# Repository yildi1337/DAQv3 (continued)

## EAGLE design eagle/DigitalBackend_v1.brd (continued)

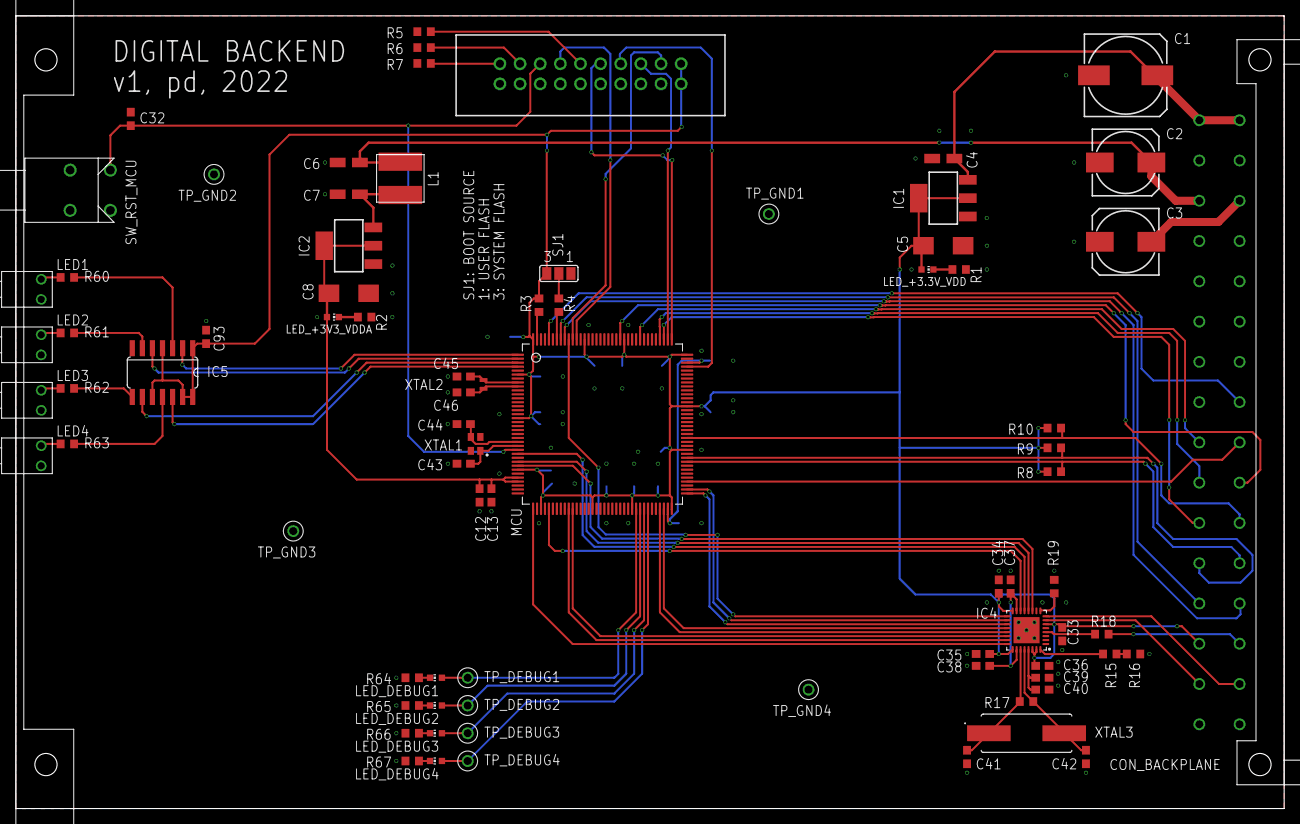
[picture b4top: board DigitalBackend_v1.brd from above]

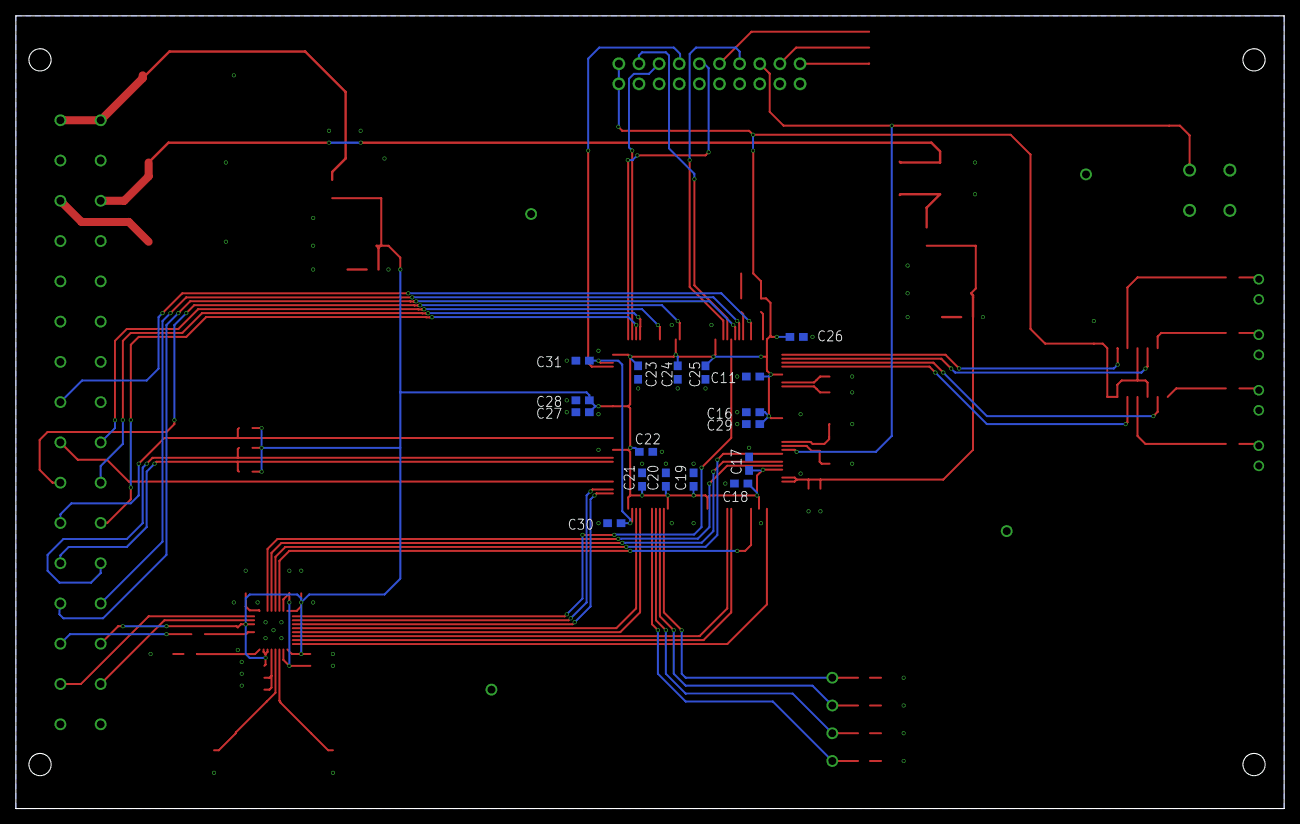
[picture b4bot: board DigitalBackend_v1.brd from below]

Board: 2 copper layers, 160.0 x 100.0 mm, 98 parts (17 on the bottom side), 80 nets.

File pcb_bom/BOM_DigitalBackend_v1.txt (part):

Stückliste exportiert aus D:/OneDrive/Elektronikprojekte/DAQ v3 STM32H7/Eagle/Digital Backend v1/DigitalBackend_v1.sch am 20.03.2022 16:16

Qty Value                           Device                          Package                         Parts                                                                                                   Description                          POPULARITY SPICEPREFIX
6                                   LEDCHIP-LED0603                 CHIP-LED0603                    LED_+3.3V_VDD, LED_+3V3_VDDA, LED_DEBUG1, LED_DEBUG2, LED_DEBUG3, LED_DEBUG4                            LED                                  26                    
4                                   RSPRO-1MM-TERMINAL-POST-2622034 RSPRO-1MM-TERMINAL-POST-2622034 TP_GND1, TP_GND2, TP_GND3, TP_GND4                                                                                                                                 
1                                   SJ2W                            SJ_2                            SJ1                                                                                                     SMD solder JUMPER                    7                     
1   09031326921                     09031326921                     09031326921                     CON_BACKPLANE                                                                                                                                                      
3   1.5k                            R-EU_R0603                      R0603                           R8, R9, R10                                                                                             RESISTOR, European symbol            70         R          
1   1.8k                            R-EU_R0603                      R0603                           R2                                                                                                      RESISTOR, European symbol            70         R          
1   1000u/16V                       CPOL-EU153CLV-1010              153CLV-1010                     C1                                                                                                      POLARIZED CAPACITOR, European symbol 0          C          
21  100n                            C-EUC0603                       C0603                           C13, C16, C17, C18, C19, C20, C21, C22, C23, C24, C25, C26, C28, C32, C33, C34, C35, C36, C37, C40, C93 CAPACITOR, European symbol           73         C          
1   100u                            VLS6045AF-101M                  VLS6045AF-101M                  L1                                                                                                                                                                 
2   100u/25V                        CPOL-EU153CLV-0810              153CLV-0810                     C2, C3                                                                                                  POLARIZED CAPACITOR, European symbol 4          C          
6   10k                             R-EU_R0603                      R0603                           R3, R4, R5, R6, R7, R16                                                                                 RESISTOR, European symbol            70         R          
3   10u                             CPOL-EUCT3216                   CT3216                          C4, C6, C7                                                                                              POLARIZED CAPACITOR, European symbol 1          C          
4   113-314-04                      113-314-04                      113-314-04                      LED1, LED2, LED3, LED4                                                                                                                                             
2   15p                             C-EUC0603                       C0603                           C45, C46                                                                                                CAPACITOR, European symbol           73         C          
1   1M                              R-EU_R0603                      R0603                           R17                                                                                                     RESISTOR, European symbol            70         R          
3   1u                              C-EUC0603                       C0603                           C11, C12, C27                                                                                           CAPACITOR, European symbol           73         C          
2   2.2u                            C-EUC0603                       C0603                           C30, C31                                                                                                CAPACITOR, European symbol           73         C          
2   22u                             CPOL-EUCT6032                   CT6032                          C5, C8                                                                                                  POLARIZED CAPACITOR, European symbol 2          C          
2   27p                             C-EUC0603                       C0603                           C41, C42                                                                                                CAPACITOR, European symbol           73         C          
1   2k                              R-EU_R0603                      R0603                           R15                                                                                                     RESISTOR, European symbol            70         R          
1   4.7k                            R-EU_R0603                      R0603                           R19                                                                                                     RESISTOR, European symbol            70         R          
3   4.7u                            C-EUC0603                       C0603                           C29, C38, C39                                                                                           CAPACITOR, European symbol           73         C          
2   5.6p                            C-EUC0603                       C0603                           C43, C44                                                                                                CAPACITOR, European symbol           73         C          
1   60807-011                       60807-011                       60807-011                       PCB_BRACKET                                                                                                                                                        
4   68                              R-EU_R0603                      R0603                           R60, R61, R62, R63                                                                                      RESISTOR, European symbol            70         R          
1   74LVC126AD,112                  74AC126D                        SO14                            IC5                                                                                                     Quad bus BUFFER, 3-state             0                     
5   750                             R-EU_R0603                      R0603                           R1, R64, R65, R66, R67                                                                                  RESISTOR, European symbol            70         R          
1   820                             R-EU_R0603                      R0603                           R18                                                                                                     RESISTOR, European symbol            70         R          
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
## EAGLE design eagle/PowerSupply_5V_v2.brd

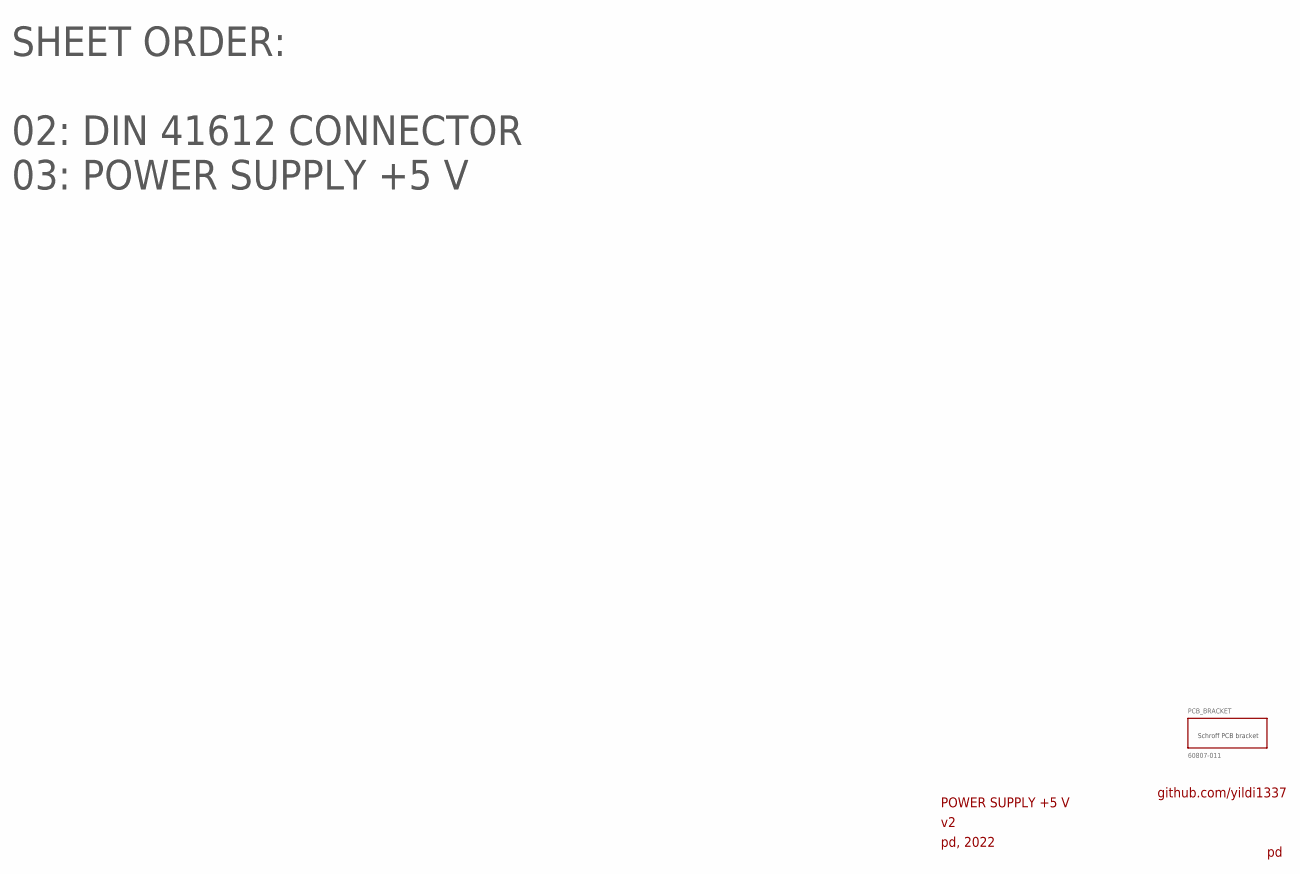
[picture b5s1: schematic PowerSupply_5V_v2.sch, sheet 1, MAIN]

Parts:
PCB_BRACKET: 60807-011

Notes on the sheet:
POWER SUPPLY +5 V
pd, 2022
github.com/yildi1337
SHEET ORDER: 02: DIN 41612 CONNECTOR 03: POWER SUPPLY +5 V

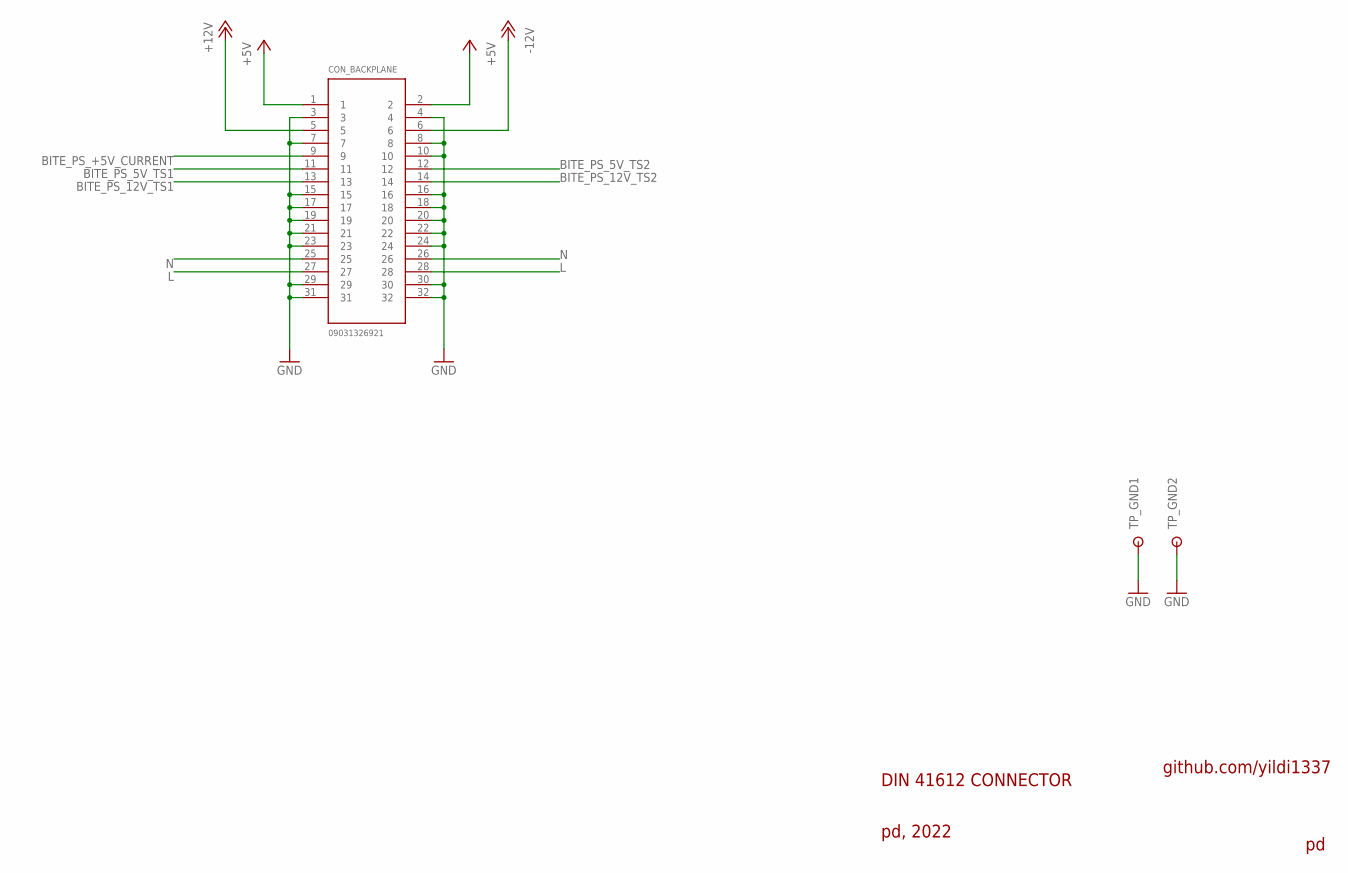
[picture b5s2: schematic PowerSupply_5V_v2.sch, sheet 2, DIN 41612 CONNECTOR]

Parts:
CON_BACKPLANE: 09031326921
TP_GND1, TP_GND2: RSPRO-1MM-TERMINAL-POST-2622034

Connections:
+5V: CON_BACKPLANE.1, CON_BACKPLANE.2; also elsewhere on the board
+12V: CON_BACKPLANE.5
-12V: CON_BACKPLANE.6
BITE_PS_5V_TS1: CON_BACKPLANE.11
BITE_PS_5V_TS2: CON_BACKPLANE.12
BITE_PS_12V_TS1: CON_BACKPLANE.13
BITE_PS_12V_TS2: CON_BACKPLANE.14
BITE_PS_+5V_CURRENT: CON_BACKPLANE.9
GND: CON_BACKPLANE.3, CON_BACKPLANE.4, CON_BACKPLANE.7, CON_BACKPLANE.8, CON_BACKPLANE.10, CON_BACKPLANE.15, CON_BACKPLANE.16, CON_BACKPLANE.17, CON_BACKPLANE.18, CON_BACKPLANE.19, CON_BACKPLANE.20, CON_BACKPLANE.21, CON_BACKPLANE.22, CON_BACKPLANE.23, CON_BACKPLANE.24, CON_BACKPLANE.29, CON_BACKPLANE.30, CON_BACKPLANE.31, CON_BACKPLANE.32, TP_GND1.P$1, TP_GND2.P$1; also elsewhere on the board
L: CON_BACKPLANE.27, CON_BACKPLANE.28; also elsewhere on the board
N: CON_BACKPLANE.25, CON_BACKPLANE.26; also elsewhere on the board

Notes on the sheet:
DIN 41612 CONNECTOR
pd, 2022
github.com/yildi1337

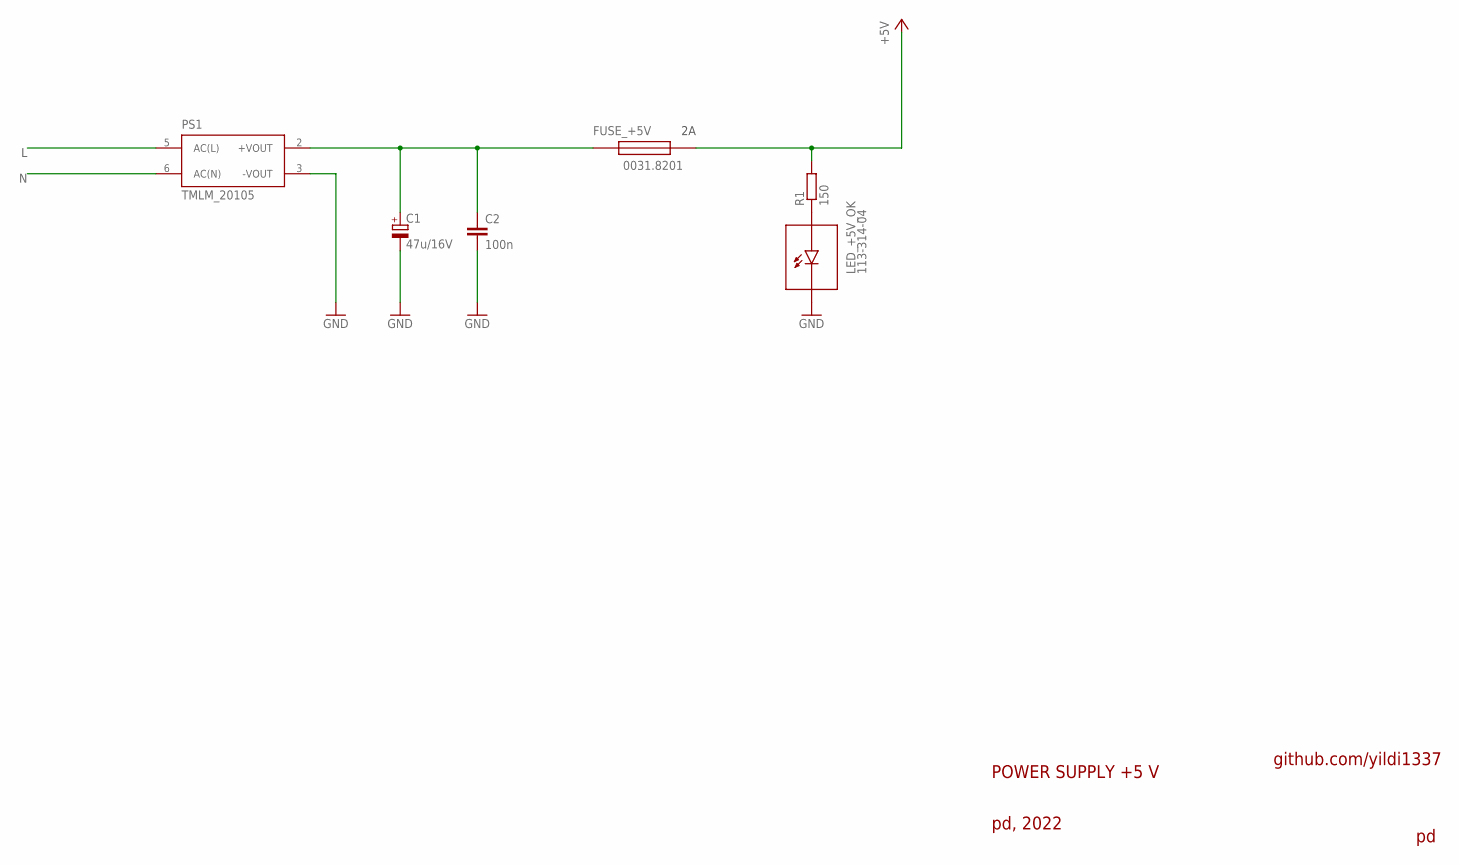
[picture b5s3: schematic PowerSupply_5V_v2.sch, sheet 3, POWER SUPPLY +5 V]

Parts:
C1: 47u/16V; 153CLV-0505
C2: 100n; C0603
FUSE_+5V: 0031.8201
LED_+5V_OK: 113-314-04
PS1: TMLM_20105; TMLM_201XX
R1: 150; R0603

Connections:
+5V: FUSE_+5V.2, R1.2; also elsewhere on the board
GND: C1.-, C2.2, LED_+5V_OK.- (C), PS1.3 (-VOUT); also elsewhere on the board
L: PS1.5 (AC(L)); also elsewhere on the board
N: PS1.6 (AC(N)); also elsewhere on the board
unnamed: C1.+, C2.1, FUSE_+5V.1, PS1.2 (+VOUT)
unnamed: LED_+5V_OK.+ (A), R1.1

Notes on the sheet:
POWER SUPPLY +5 V
pd, 2022
github.com/yildi1337

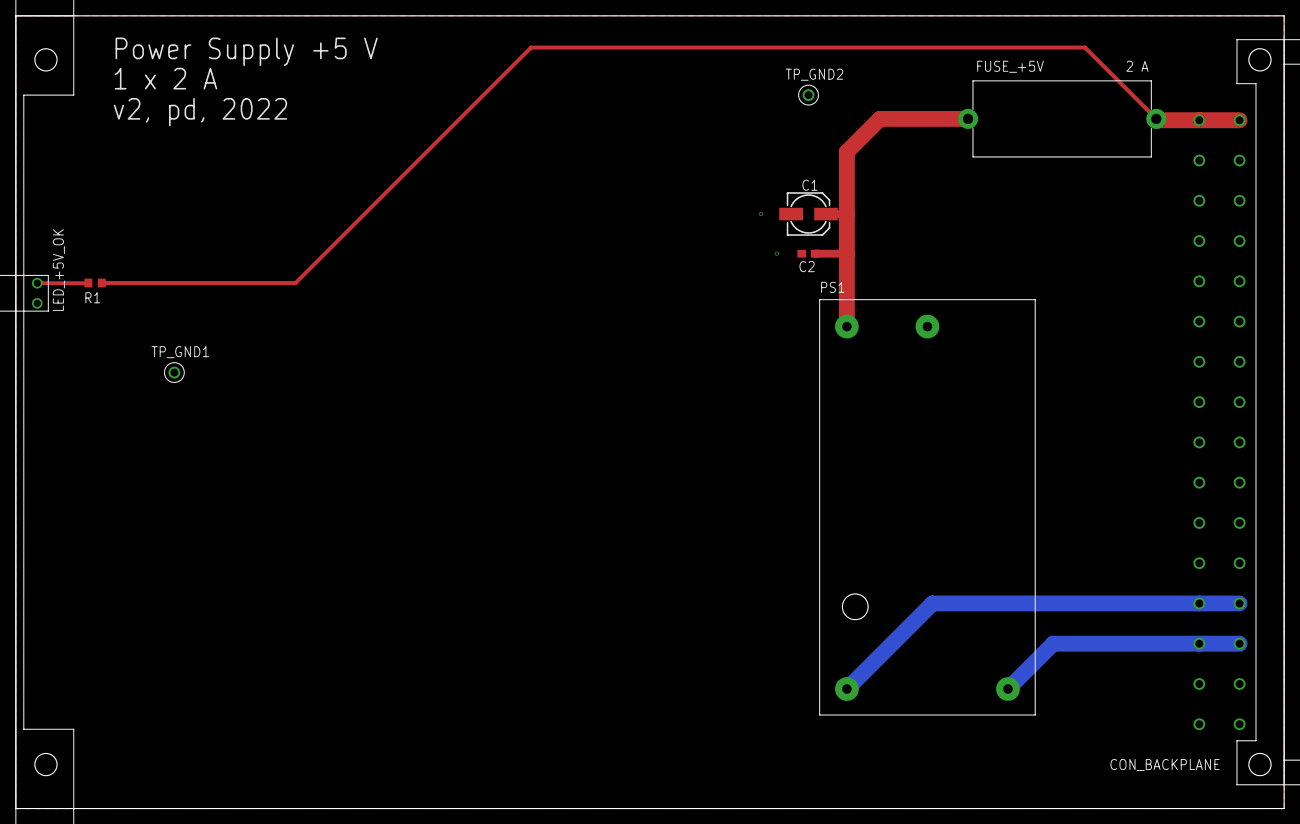
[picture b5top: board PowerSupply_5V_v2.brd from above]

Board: 2 copper layers, 160.0 x 100.0 mm, 10 parts (0 on the bottom side), 6 nets.

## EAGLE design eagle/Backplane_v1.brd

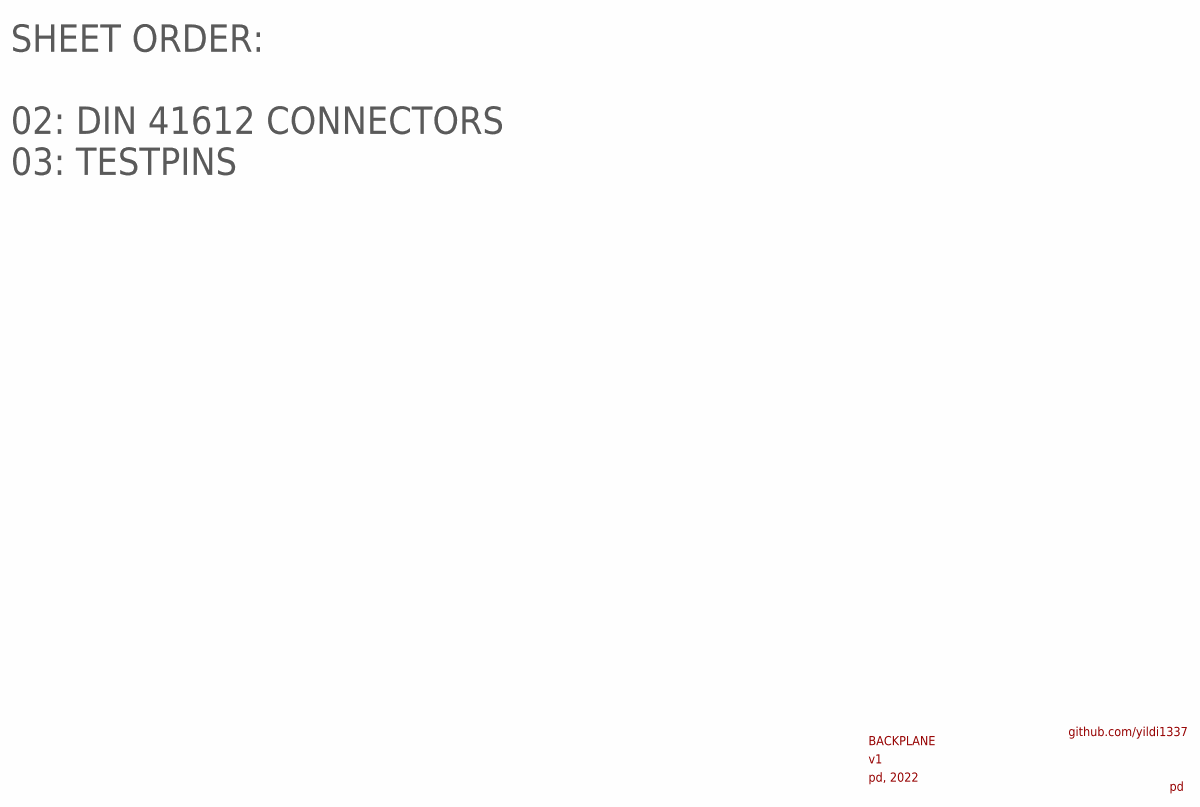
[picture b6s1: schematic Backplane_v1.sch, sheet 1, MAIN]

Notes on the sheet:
BACKPLANE
pd, 2022
github.com/yildi1337
SHEET ORDER: 02: DIN 41612 CONNECTORS 03: TESTPINS

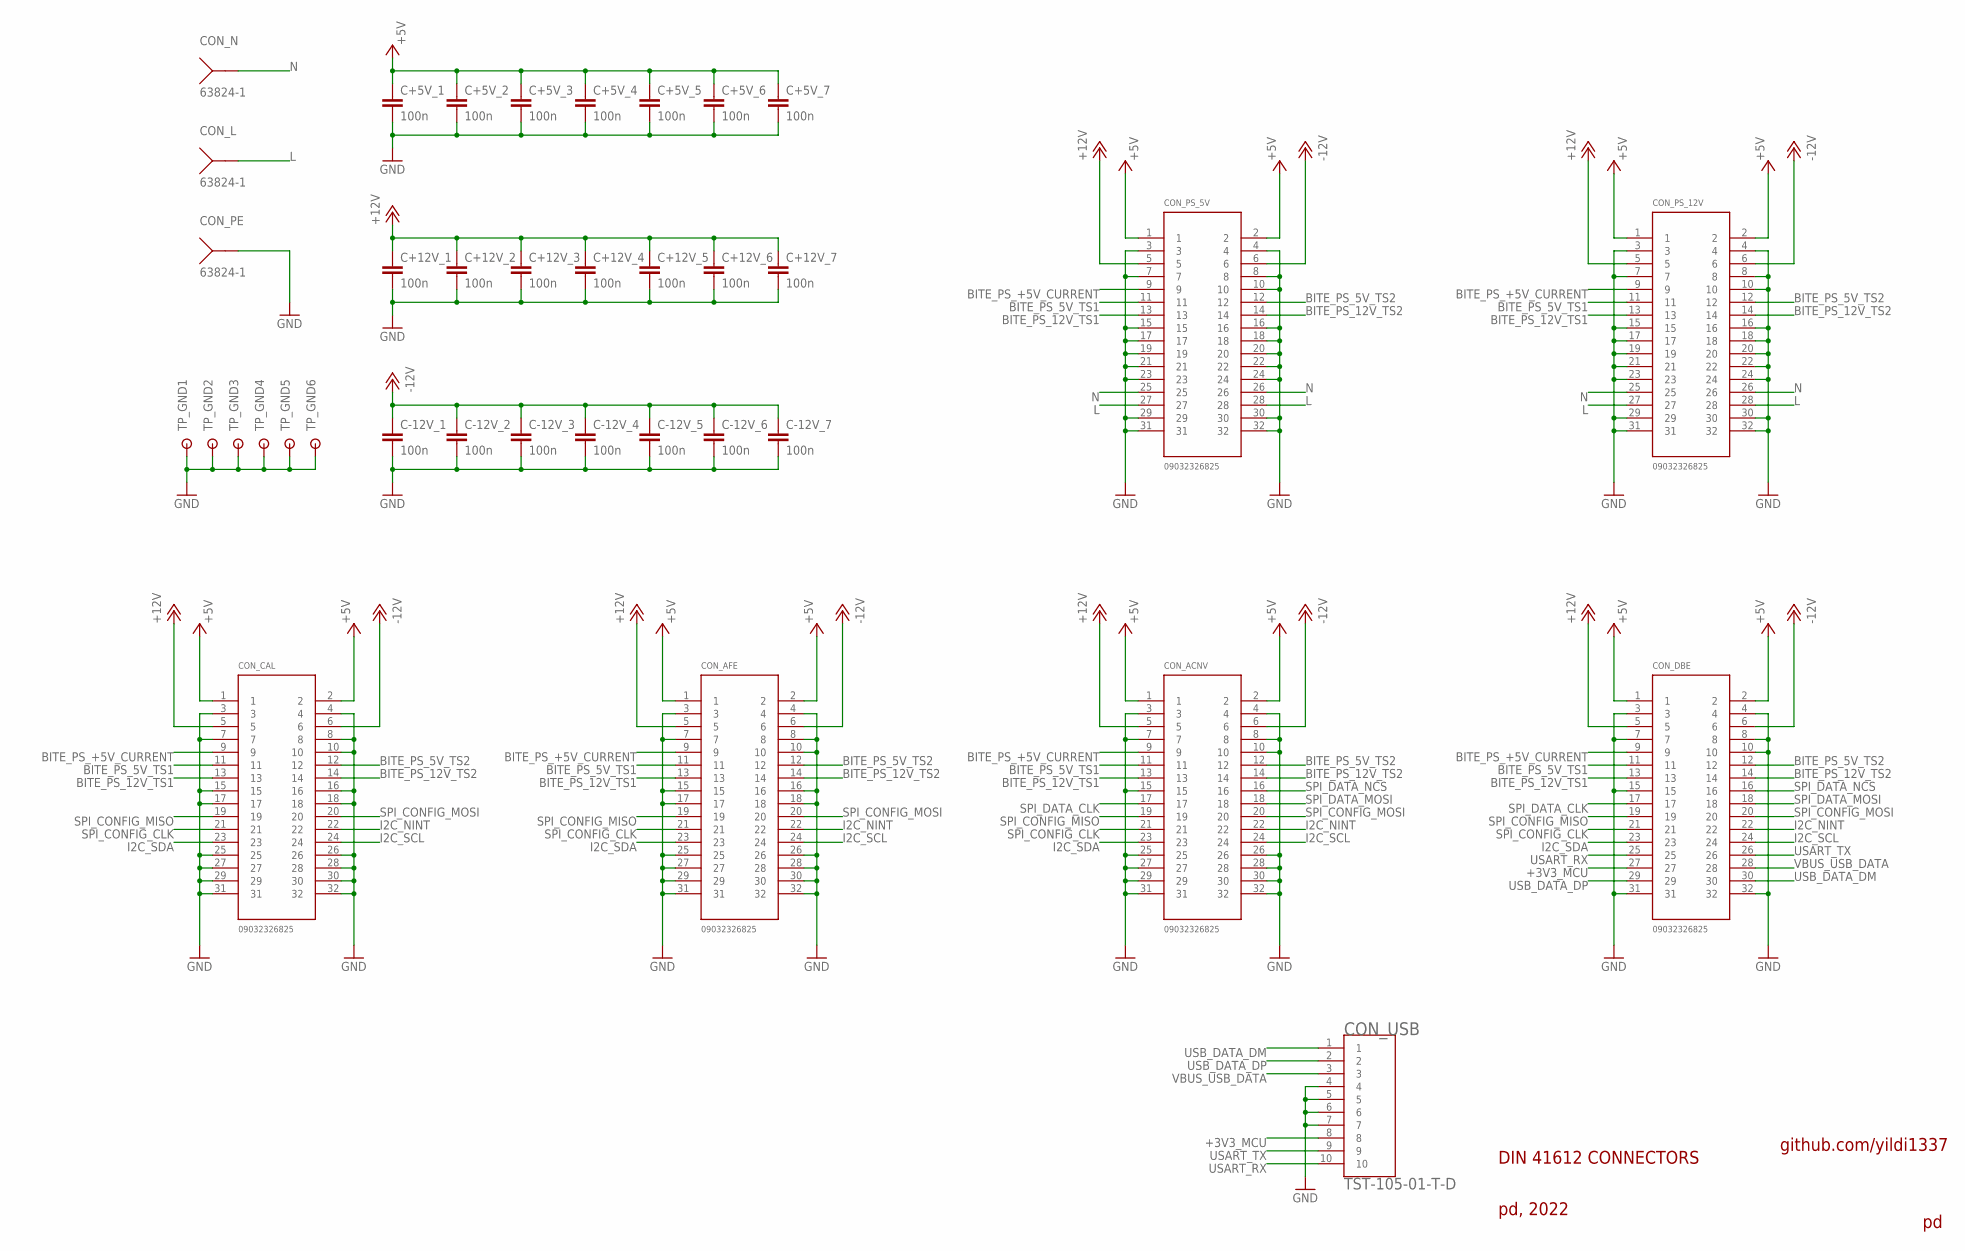
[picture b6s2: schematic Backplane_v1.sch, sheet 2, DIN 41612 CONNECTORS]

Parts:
C+5V_1, C+5V_2, C+5V_3, C+5V_4, C+5V_5, C+5V_6, C+5V_7, C+12V_1, C+12V_2, C+12V_3, C+12V_4, C+12V_5, C+12V_6, C+12V_7: 100n; C0603
C-12V_1, C-12V_2, C-12V_3, C-12V_4, C-12V_5, C-12V_6, C-12V_7: 100n; C0603
CON_ACNV: 09032326825
CON_AFE: 09032326825
CON_CAL: 09032326825
CON_DBE: 09032326825
CON_L: 63824-1
CON_N: 63824-1
CON_PE: 63824-1
CON_PS_5V, CON_PS_12V: 09032326825
CON_USB: TST-105-01-T-D
TP_GND1, TP_GND2, TP_GND3, TP_GND4, TP_GND5, TP_GND6: RSPRO-1MM-TERMINAL-POST-2622034

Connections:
+3V3_MCU: CON_DBE.27, CON_USB.8; also elsewhere on the board
+5V: C+5V_1.1, C+5V_2.1, C+5V_3.1, C+5V_4.1, C+5V_5.1, C+5V_6.1, C+5V_7.1, CON_ACNV.1, CON_ACNV.2, CON_AFE.1, CON_AFE.2, CON_CAL.1, CON_CAL.2, CON_DBE.1, CON_DBE.2, CON_PS_5V.1, CON_PS_5V.2, CON_PS_12V.1, CON_PS_12V.2; also elsewhere on the board
+12V: C+12V_1.1, C+12V_2.1, C+12V_3.1, C+12V_4.1, C+12V_5.1, C+12V_6.1, C+12V_7.1, CON_ACNV.5, CON_AFE.5, CON_CAL.5, CON_DBE.5, CON_PS_5V.5, CON_PS_12V.5; also elsewhere on the board
-12V: C-12V_1.1, C-12V_2.1, C-12V_3.1, C-12V_4.1, C-12V_5.1, C-12V_6.1, C-12V_7.1, CON_ACNV.6, CON_AFE.6, CON_CAL.6, CON_DBE.6, CON_PS_5V.6, CON_PS_12V.6; also elsewhere on the board
BITE_PS_5V_TS1: CON_ACNV.11, CON_AFE.11, CON_CAL.11, CON_DBE.11, CON_PS_5V.11, CON_PS_12V.11; also elsewhere on the board
BITE_PS_5V_TS2: CON_ACNV.12, CON_AFE.12, CON_CAL.12, CON_DBE.12, CON_PS_5V.12, CON_PS_12V.12; also elsewhere on the board
BITE_PS_12V_TS1: CON_ACNV.13, CON_AFE.13, CON_CAL.13, CON_DBE.13, CON_PS_5V.13, CON_PS_12V.13; also elsewhere on the board
BITE_PS_12V_TS2: CON_ACNV.14, CON_AFE.14, CON_CAL.14, CON_DBE.14, CON_PS_5V.14, CON_PS_12V.14; also elsewhere on the board
BITE_PS_+5V_CURRENT: CON_ACNV.9, CON_AFE.9, CON_CAL.9, CON_DBE.9, CON_PS_5V.9, CON_PS_12V.9; also elsewhere on the board
GND: C+5V_1.2, C+5V_2.2, C+5V_3.2, C+5V_4.2, C+5V_5.2, C+5V_6.2, C+5V_7.2, C+12V_1.2, C+12V_2.2, C+12V_3.2, C+12V_4.2, C+12V_5.2, C+12V_6.2, C+12V_7.2, C-12V_1.2, C-12V_2.2, C-12V_3.2, C-12V_4.2, C-12V_5.2, C-12V_6.2, C-12V_7.2, CON_ACNV.3, CON_ACNV.4, CON_ACNV.7, CON_ACNV.8, CON_ACNV.10, CON_ACNV.15, CON_ACNV.25, CON_ACNV.26, CON_ACNV.27, CON_ACNV.28, CON_ACNV.29, CON_ACNV.30, CON_ACNV.31, CON_ACNV.32, CON_AFE.3, CON_AFE.4, CON_AFE.7, CON_AFE.8, CON_AFE.10, CON_AFE.15, CON_AFE.16, CON_AFE.17, CON_AFE.18, CON_AFE.25, CON_AFE.26, CON_AFE.27, CON_AFE.28, CON_AFE.29, CON_AFE.30, CON_AFE.31, CON_AFE.32, CON_CAL.3, CON_CAL.4, CON_CAL.7, CON_CAL.8, CON_CAL.10, CON_CAL.15, CON_CAL.16, CON_CAL.17, CON_CAL.18, CON_CAL.25, CON_CAL.26, CON_CAL.27, CON_CAL.28, CON_CAL.29, CON_CAL.30, CON_CAL.31, CON_CAL.32, CON_DBE.3, CON_DBE.4, CON_DBE.7, CON_DBE.8, CON_DBE.10, CON_DBE.15, CON_DBE.31, CON_DBE.32, CON_PE.1, CON_PE.2, CON_PS_5V.3, CON_PS_5V.4, CON_PS_5V.7, CON_PS_5V.8, CON_PS_5V.10, CON_PS_5V.15, CON_PS_5V.16, CON_PS_5V.17, CON_PS_5V.18, CON_PS_5V.19, CON_PS_5V.20, CON_PS_5V.21, CON_PS_5V.22, CON_PS_5V.23, CON_PS_5V.24, CON_PS_5V.29, CON_PS_5V.30, CON_PS_5V.31, CON_PS_5V.32, CON_PS_12V.3, CON_PS_12V.4, CON_PS_12V.7, CON_PS_12V.8, CON_PS_12V.10, CON_PS_12V.15, CON_PS_12V.16, CON_PS_12V.17, CON_PS_12V.18, CON_PS_12V.19, CON_PS_12V.20, CON_PS_12V.21, CON_PS_12V.22, CON_PS_12V.23, CON_PS_12V.24, CON_PS_12V.29, CON_PS_12V.30, CON_PS_12V.31, CON_PS_12V.32, CON_USB.4, CON_USB.5, CON_USB.6, CON_USB.7, TP_GND1.P$1, TP_GND2.P$1, TP_GND3.P$1, TP_GND4.P$1, TP_GND5.P$1, TP_GND6.P$1
I2C_NINT: CON_ACNV.22, CON_AFE.22, CON_CAL.22, CON_DBE.22; also elsewhere on the board
I2C_SCL: CON_ACNV.24, CON_AFE.24, CON_CAL.24, CON_DBE.24; also elsewhere on the board
I2C_SDA: CON_ACNV.23, CON_AFE.23, CON_CAL.23, CON_DBE.23; also elsewhere on the board
L: CON_L.1, CON_L.2, CON_PS_5V.27, CON_PS_5V.28, CON_PS_12V.27, CON_PS_12V.28
N: CON_N.1, CON_N.2, CON_PS_5V.25, CON_PS_5V.26, CON_PS_12V.25, CON_PS_12V.26
SPI_CONFIG_CLK: CON_ACNV.21, CON_AFE.21, CON_CAL.21, CON_DBE.21; also elsewhere on the board
SPI_CONFIG_MISO: CON_ACNV.19, CON_AFE.19, CON_CAL.19, CON_DBE.19; also elsewhere on the board
SPI_CONFIG_MOSI: CON_ACNV.20, CON_AFE.20, CON_CAL.20, CON_DBE.20; also elsewhere on the board
SPI_DATA_CLK: CON_ACNV.17, CON_DBE.17; also elsewhere on the board
SPI_DATA_MOSI: CON_ACNV.18, CON_DBE.18; also elsewhere on the board
SPI_DATA_NCS: CON_ACNV.16, CON_DBE.16; also elsewhere on the board
USART_RX: CON_DBE.25, CON_USB.10; also elsewhere on the board
USART_TX: CON_DBE.26, CON_USB.9; also elsewhere on the board
USB_DATA_DM: CON_DBE.30, CON_USB.1; also elsewhere on the board
USB_DATA_DP: CON_DBE.29, CON_USB.2; also elsewhere on the board
VBUS_USB_DATA: CON_DBE.28, CON_USB.3; also elsewhere on the board

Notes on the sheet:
DIN 41612 CONNECTORS
pd, 2022
github.com/yildi1337

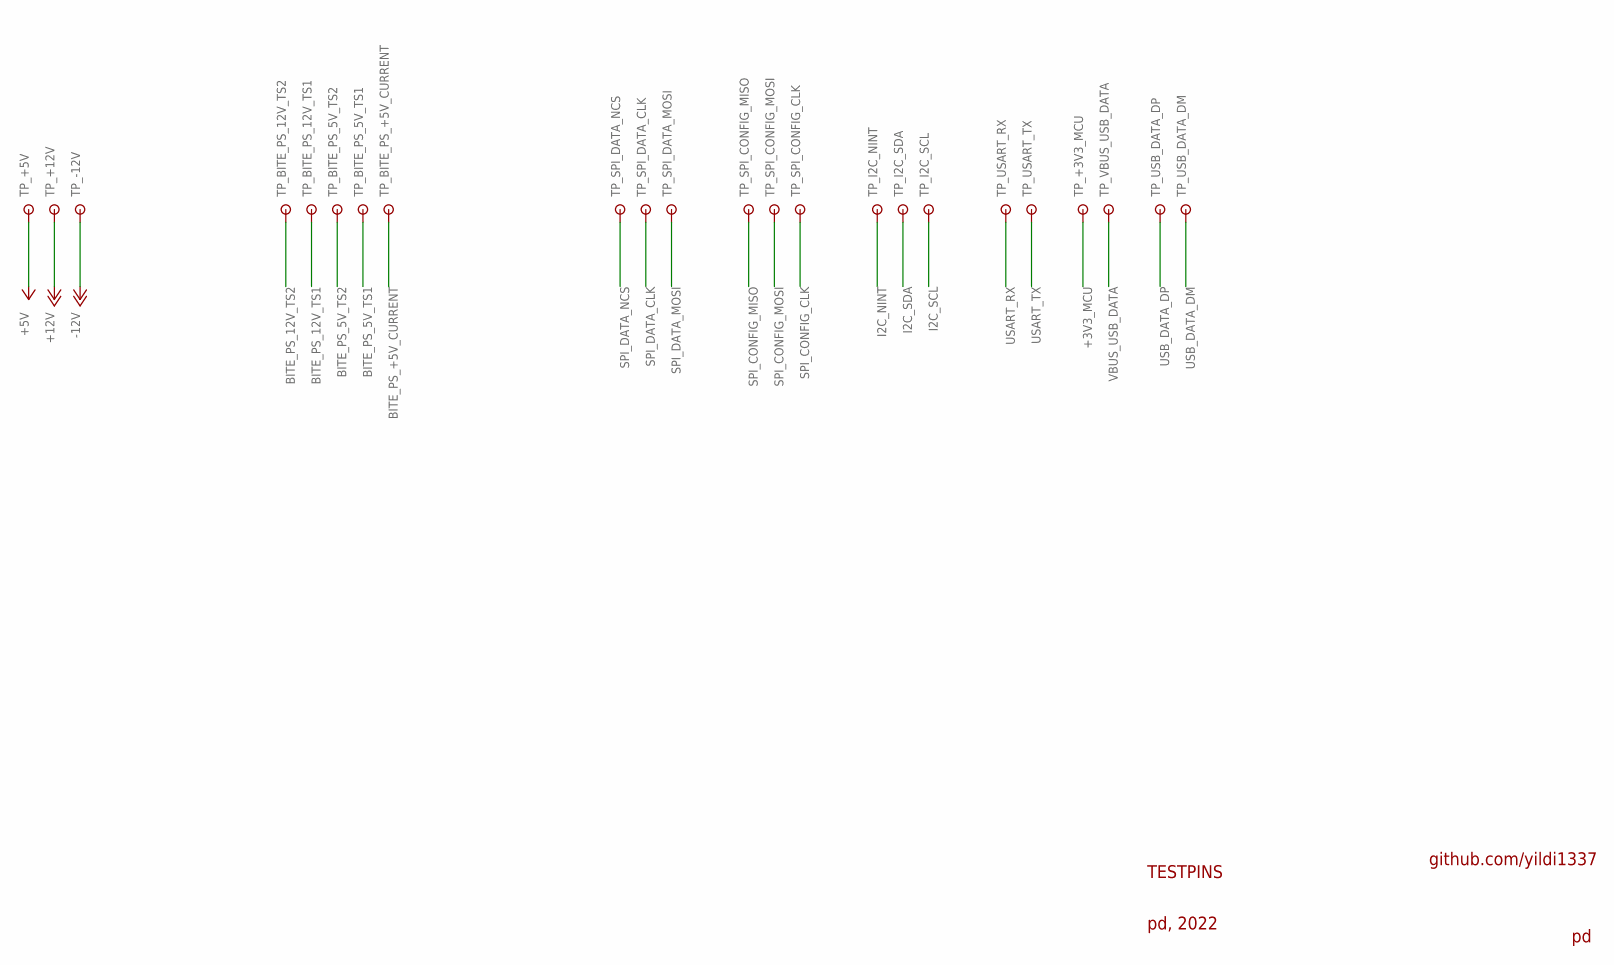
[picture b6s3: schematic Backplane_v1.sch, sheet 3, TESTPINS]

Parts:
TP_+3V3_MCU, TP_+5V, TP_+12V: RSPRO-1MM-TERMINAL-POST-2622034
TP_-12V: RSPRO-1MM-TERMINAL-POST-2622034
TP_BITE_PS_5V_TS1, TP_BITE_PS_5V_TS2, TP_BITE_PS_12V_TS1, TP_BITE_PS_12V_TS2: RSPRO-1MM-TERMINAL-POST-2622034
TP_BITE_PS_+5V_CURRENT: RSPRO-1MM-TERMINAL-POST-2622034
TP_I2C_NINT, TP_I2C_SCL, TP_I2C_SDA: RSPRO-1MM-TERMINAL-POST-2622034
TP_SPI_CONFIG_CLK: RSPRO-1MM-TERMINAL-POST-2622034
TP_SPI_CONFIG_MISO: RSPRO-1MM-TERMINAL-POST-2622034
TP_SPI_CONFIG_MOSI: RSPRO-1MM-TERMINAL-POST-2622034
TP_SPI_DATA_CLK: RSPRO-1MM-TERMINAL-POST-2622034
TP_SPI_DATA_MOSI: RSPRO-1MM-TERMINAL-POST-2622034
TP_SPI_DATA_NCS: RSPRO-1MM-TERMINAL-POST-2622034
TP_USART_RX: RSPRO-1MM-TERMINAL-POST-2622034
TP_USART_TX: RSPRO-1MM-TERMINAL-POST-2622034
TP_USB_DATA_DM: RSPRO-1MM-TERMINAL-POST-2622034
TP_USB_DATA_DP: RSPRO-1MM-TERMINAL-POST-2622034
TP_VBUS_USB_DATA: RSPRO-1MM-TERMINAL-POST-2622034

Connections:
+3V3_MCU: TP_+3V3_MCU.P$1; also elsewhere on the board
+5V: TP_+5V.P$1; also elsewhere on the board
+12V: TP_+12V.P$1; also elsewhere on the board
-12V: TP_-12V.P$1; also elsewhere on the board
BITE_PS_5V_TS1: TP_BITE_PS_5V_TS1.P$1; also elsewhere on the board
BITE_PS_5V_TS2: TP_BITE_PS_5V_TS2.P$1; also elsewhere on the board
BITE_PS_12V_TS1: TP_BITE_PS_12V_TS1.P$1; also elsewhere on the board
BITE_PS_12V_TS2: TP_BITE_PS_12V_TS2.P$1; also elsewhere on the board
BITE_PS_+5V_CURRENT: TP_BITE_PS_+5V_CURRENT.P$1; also elsewhere on the board
I2C_NINT: TP_I2C_NINT.P$1; also elsewhere on the board
I2C_SCL: TP_I2C_SCL.P$1; also elsewhere on the board
I2C_SDA: TP_I2C_SDA.P$1; also elsewhere on the board
SPI_CONFIG_CLK: TP_SPI_CONFIG_CLK.P$1; also elsewhere on the board
SPI_CONFIG_MISO: TP_SPI_CONFIG_MISO.P$1; also elsewhere on the board
SPI_CONFIG_MOSI: TP_SPI_CONFIG_MOSI.P$1; also elsewhere on the board
SPI_DATA_CLK: TP_SPI_DATA_CLK.P$1; also elsewhere on the board
SPI_DATA_MOSI: TP_SPI_DATA_MOSI.P$1; also elsewhere on the board
SPI_DATA_NCS: TP_SPI_DATA_NCS.P$1; also elsewhere on the board
USART_RX: TP_USART_RX.P$1; also elsewhere on the board
USART_TX: TP_USART_TX.P$1; also elsewhere on the board
USB_DATA_DM: TP_USB_DATA_DM.P$1; also elsewhere on the board
USB_DATA_DP: TP_USB_DATA_DP.P$1; also elsewhere on the board
VBUS_USB_DATA: TP_VBUS_USB_DATA.P$1; also elsewhere on the board

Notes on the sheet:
TESTPINS
pd, 2022
github.com/yildi1337
